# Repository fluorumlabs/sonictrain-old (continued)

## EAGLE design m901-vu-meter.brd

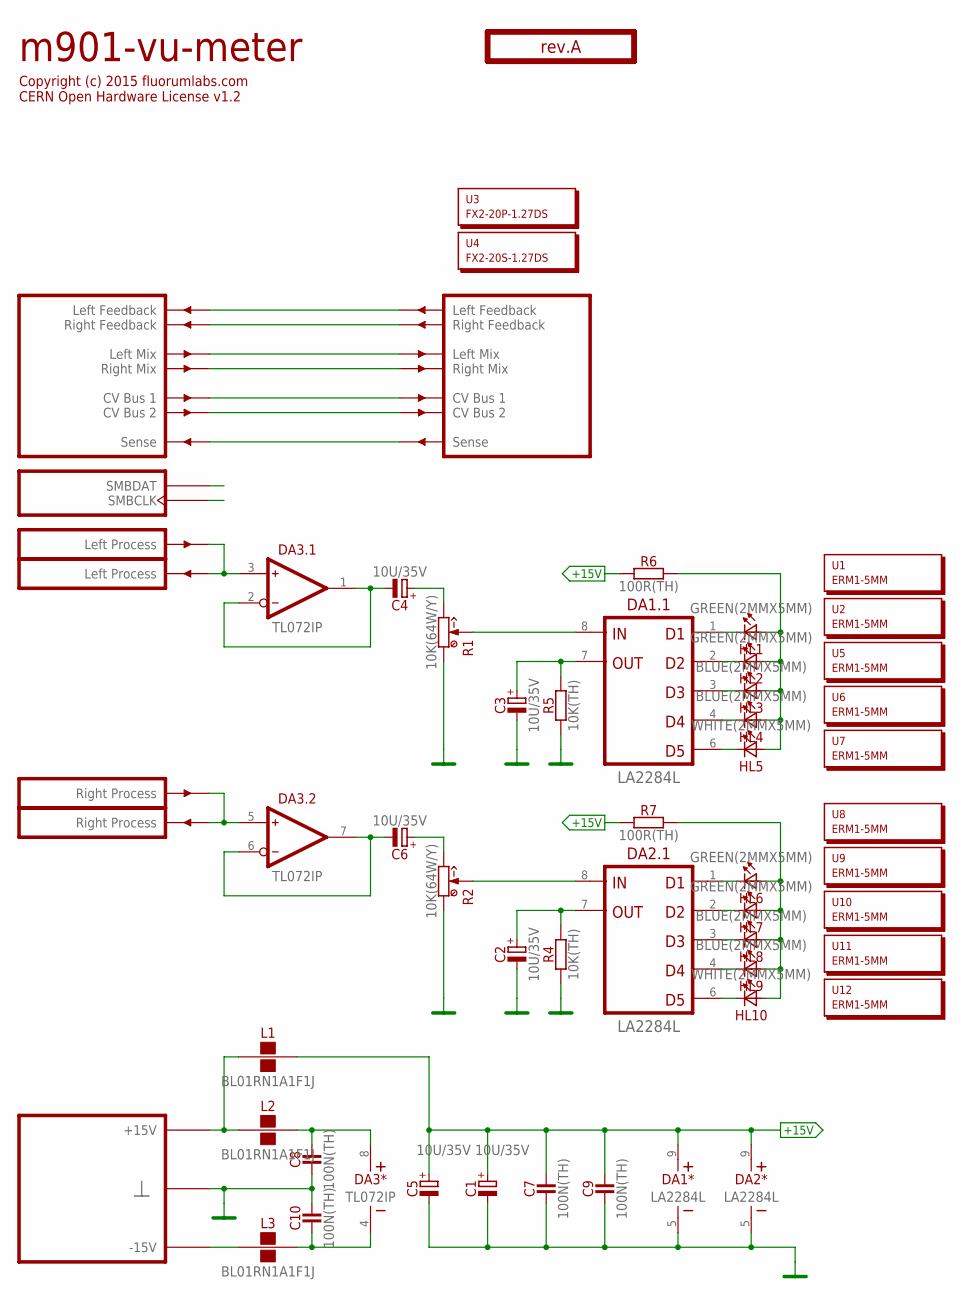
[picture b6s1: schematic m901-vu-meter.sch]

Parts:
C1, C2, C3, C4, C5, C6: 10U/35V; E2-5
C7, C8, C9, C10: 100N(TH); C050-024X044
DA1, DA2: LA2284L; SIL9
DA3: TL072IP; DIP-8
HL1, HL2, HL6, HL7: GREEN(2MMX5MM); LED2X5
HL3, HL4, HL8, HL9: BLUE(2MMX5MM); LED2X5
HL5, HL10: WHITE(2MMX5MM); LED2X5
L1, L2, L3: BL01RN1A1F1J; BL01RN1A
O1: TITLE; EMPTY
PCB1: rev.A; ST2-BOARD-26
R1, R2: 10K(64W/Y); 64W
R4, R5: 10K(TH); R-0207/10
R6, R7: 100R(TH); R-0207/10
U1, U2, U5, U6, U7, U8, U9, U10, U11, U12: ERM1-5MM; EMPTY
U3: FX2-20P-1.27DS; EMPTY
U4: FX2-20S-1.27DS; EMPTY

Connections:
+15V: C1.+, C5.+, C7.2, C9.2, DA1.9 (V+), DA2.9 (V+), L1.2, R6.1, R7.1
GND: C1.-, C2.-, C3.-, C5.-, C7.1, C8.1, C9.1, C10.2, DA1.5 (V-), DA2.5 (V-), PCB1.B4 (GND), PCB1.B4' (GND), PCB1.B5 (GND), PCB1.B5' (GND), PCB1.B6 (GND), PCB1.B6' (GND), PCB1.B7 (GND), PCB1.B7' (GND), PCB1.B8 (GND), PCB1.B8' (GND), R1.1 (CCW), R2.1 (CCW), R4.1, R5.1
LMIX: PCB1.ALMIX (LMIX), PCB1.ALMIX' (LMIX')
unnamed: L1.1, L2.1, PCB1.A+15 (P+15V), PCB1.A+15' (P+15V), PCB1.B+15 (P+15V), PCB1.B+15' (P+15V)
unnamed: PCB1.ALFBK (LFBK), PCB1.ALFBK' (LFBK')
unnamed: DA2.8 (IN), R2.S (W), R2.S@1 (W)
unnamed: PCB1.ARFBK (RFBK), PCB1.ARFBK' (RFBK')
unnamed: DA1.8 (IN), R1.S (W), R1.S@1 (W)
unnamed: C3.+, DA1.7 (OUT), R5.2
unnamed: C2.+, DA2.7 (OUT), R4.2
unnamed: HL1.A, HL2.A, HL3.A, HL4.A, HL5.A, R6.2
unnamed: DA1.1 (D1), HL1.K (C)
unnamed: DA1.2 (D2), HL2.K (C)
unnamed: DA1.3 (D3), HL3.K (C)
unnamed: DA1.4 (D4), HL4.K (C)
unnamed: DA1.6 (D5), HL5.K (C)
unnamed: HL6.A, HL7.A, HL8.A, HL9.A, HL10.A, R7.2
unnamed: DA2.1 (D1), HL6.K (C)
unnamed: PCB1.BSENSE (SENSE), PCB1.BSENSE' (SENSE')
unnamed: DA2.2 (D2), HL7.K (C)
unnamed: DA2.3 (D3), HL8.K (C)
unnamed: DA2.4 (D4), HL9.K (C)
unnamed: DA2.6 (D5), HL10.K (C)
unnamed: C4.+, R1.3 (CW)
unnamed: C6.+, R2.3 (CW)
unnamed: DA3.3 (IN+), PCB1.BINL (INL), PCB1.BOUTL' (OUTL)
unnamed: DA3.5 (IN+), PCB1.BINR (INR), PCB1.BOUTR' (OUTR)
unnamed: L3.1, PCB1.A-15 (P-15V), PCB1.A-15' (P-15V), PCB1.B-15 (P-15V), PCB1.B-15' (P-15V)
unnamed: C8.2, DA3.8 (V+), L2.2
unnamed: C10.1, DA3.4 (V-), L3.2
unnamed: C4.-, DA3.1 (OUT), DA3.2 (IN-)
unnamed: C6.-, DA3.6 (IN-), DA3.7 (OUT)
unnamed: PCB1.ASMBDAT (SMBDAT), PCB1.ASMBDAT' (SMBDAT)
unnamed: PCB1.ACV1 (CV1), PCB1.ACV1' (CV1')
unnamed: PCB1.ACV2 (CV2), PCB1.ACV2' (CV2')
unnamed: PCB1.ASMBCLK (SMBCLK), PCB1.ASMBCLK' (SMBCLK)
RMIX: PCB1.ARMIX (RMIX), PCB1.ARMIX' (RMIX')

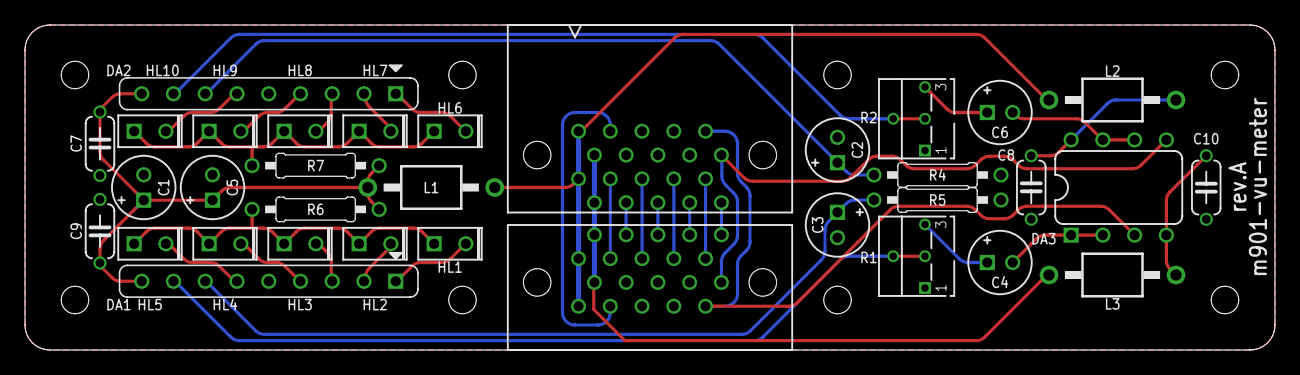
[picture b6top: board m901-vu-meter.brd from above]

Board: 2 copper layers, 100.0 x 26.0 mm, 46 parts (0 on the bottom side), 37 nets.
